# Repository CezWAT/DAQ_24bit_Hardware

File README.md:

# DAQ_24bit
Simple 4 channel 24bit USB DAQ
Uses ADS122U04 ADC and MCP2200 UART/GPIO - USB converter. No Dedicated uC.
4 Input channels with 4 ranges (+- 1V, 2V, 10V, 25V) and 2 current output channels.

Project for fun and curiosity with a purpose to make a simple yte precise USB DAQ without a dedicated controller requireig firmware. 

Forked to add an Eagle based pcb made by myself.

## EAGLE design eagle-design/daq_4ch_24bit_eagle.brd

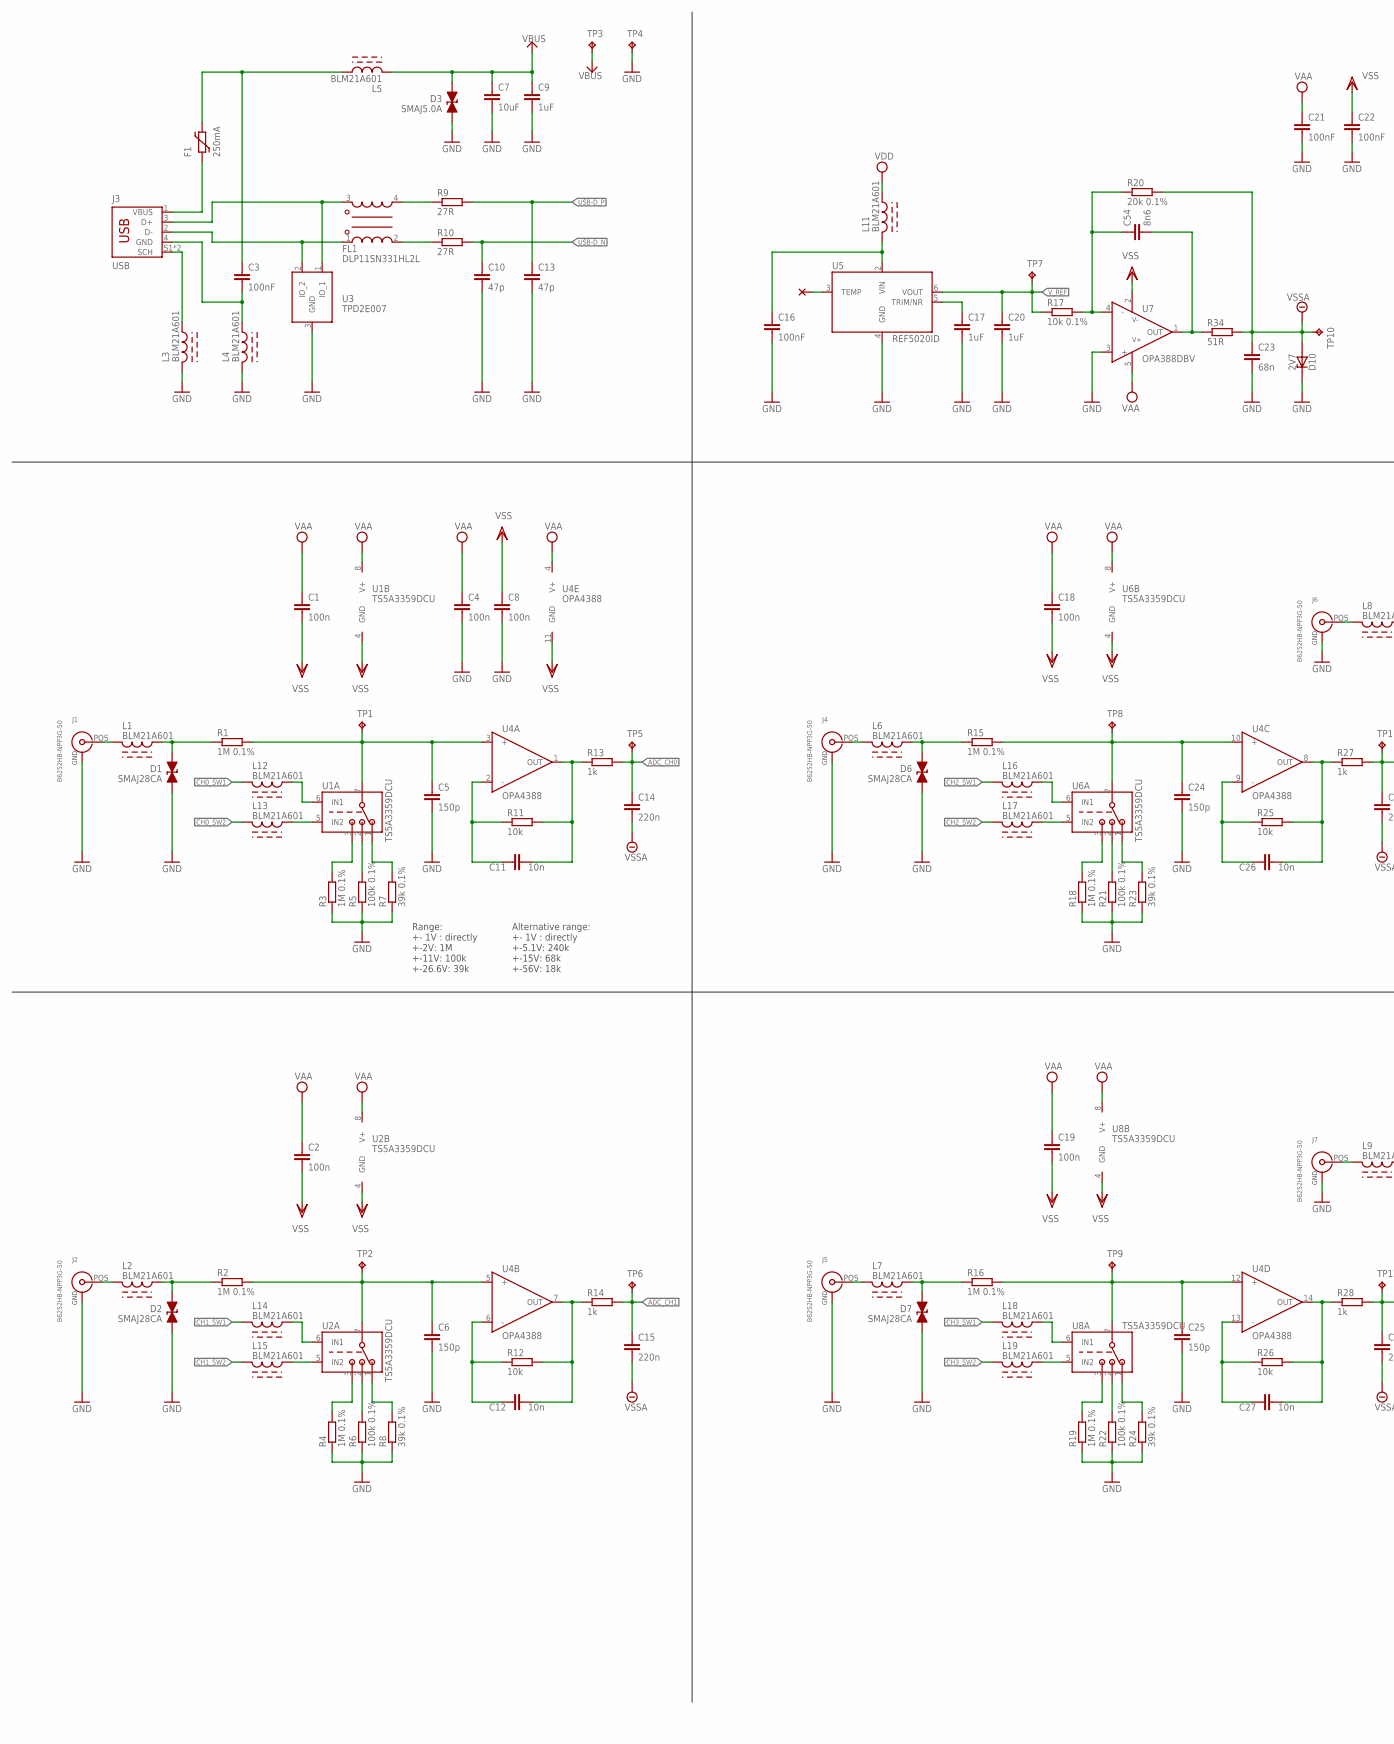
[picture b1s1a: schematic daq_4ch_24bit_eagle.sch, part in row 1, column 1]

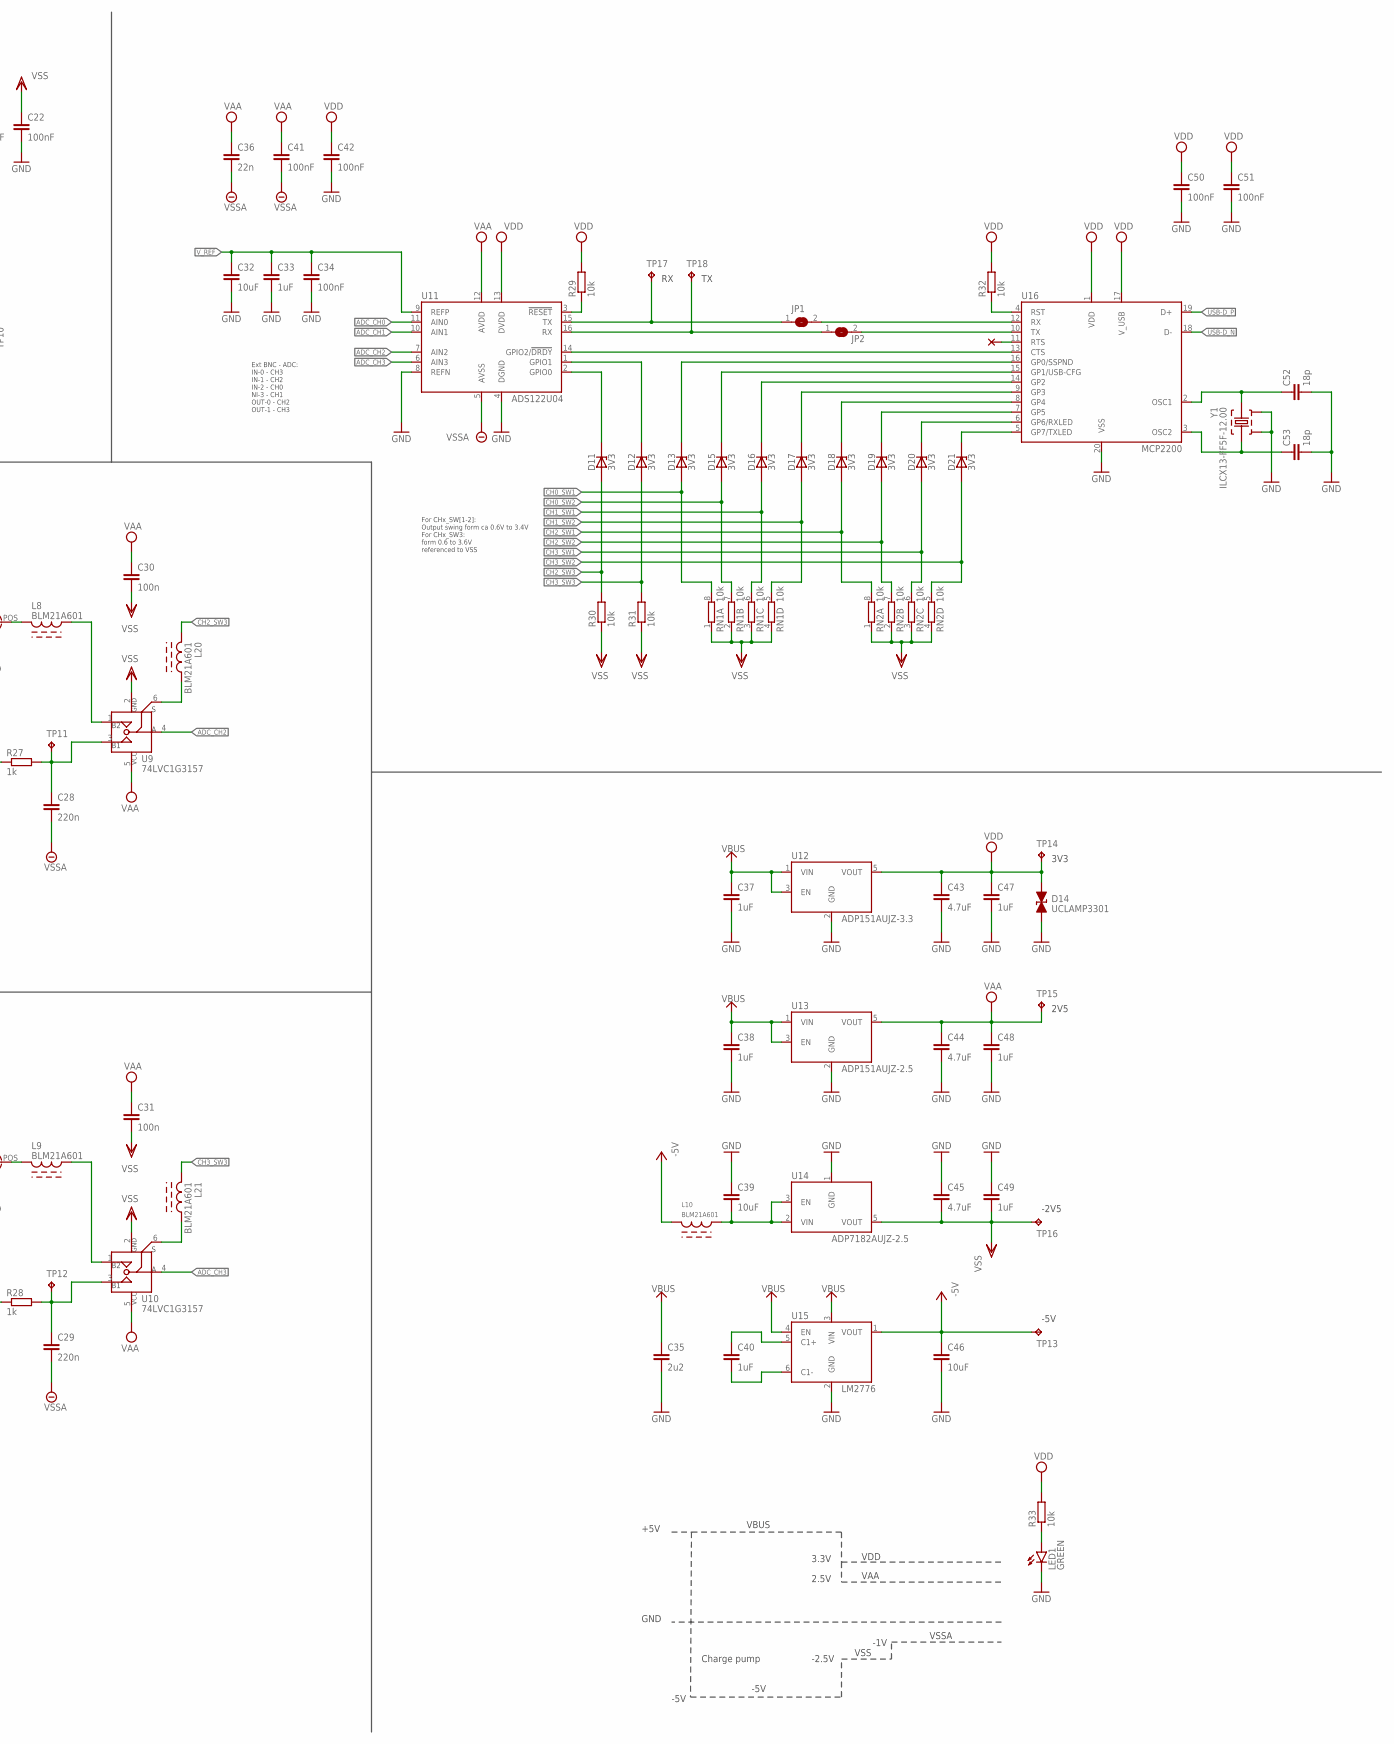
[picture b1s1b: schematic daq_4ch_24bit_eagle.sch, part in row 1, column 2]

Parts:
C1, C2, C4, C8, C18, C19, C30, C31: 100n; C0603
C3, C16, C21, C22, C34, C41, C42, C50, C51: 100nF; C0603
C5, C6, C24, C25: 150p; C0603
C7, C32, C39, C46: 10uF; C0603
C9, C17, C20, C33, C37, C38, C40, C47, C48, C49: 1uF; C0603
C10, C13: 47p; C0603
C11, C12, C26, C27: 10n; C0603
C14, C15, C28, C29: 220n; C0603
C23: 68n; C0603
C35: 2u2; C0603
C36: 22n; C0603
C43, C44, C45: 4.7uF; C0603
C52, C53: 18p; C0603
C54: 8n6; C0603
D1, D2, D6, D7: SMAJ28CA; SMA(UNI)
D3: SMAJ5.0A; SMA(UNI)
D10: 2V7; SOD323
D11, D12, D13, D15, D16, D17, D18, D19, D20, D21: 3V3; SOD323
D14: UCLAMP3301; SOD323
F1: 250mA; 1812L
FL1: DLP11SN331HL2L
J1, J2, J4, J5, J6, J7: B6252HB-NPP3G-50
J3: USB; USB_B_THT
JP1, JP2: SJ
L1, L2, L3, L4, L5, L6, L7, L8, L9, L10, L11, L12, L13, L14, L15, L16, L17, L18, L19, L20, L21: BLM21A601; L0805
LED1: GREEN; LED5MM
R1, R2, R3, R4, R15, R16, R18, R19: 1M 0.1%; R0603
R5, R6, R21, R22: 100k 0.1%; R0603
R7, R8, R23, R24: 39k 0.1%; R0603
R9, R10: 27R; R0603
R11, R12, R25, R26, R29, R30, R31, R32, R33: 10k; R0603
R13, R14, R27, R28: 1k; R0603
R17: 10k 0.1%; R0603
R20: 20k 0.1%; R0603
R34: 51R; R0603
RN1, RN2: 10k; 0603-ARV
TP1, TP2, TP3, TP4, TP5, TP6, TP7, TP8, TP9, TP10, TP11, TP12, TP14: 3V3; B1,27
TP13: -5V; B1,27
TP15: 2V5; B1,27
TP16: -2V5; B1,27
TP17: RX; B1,27
TP18: TX; B1,27
U1, U2, U6, U8: TS5A3359DCU; DCU
U3: TPD2E007; SOT323
U4: OPA4388; SOIC14
U5: REF5020ID; SOIC8
U7: OPA388DBV; SOT23-5
U9, U10: 74LVC1G3157; SOT23-6
U11: ADS122U04; SSOP16
U12: ADP151AUJZ-3.3; SOT23-5
U13: ADP151AUJZ-2.5; SOT23-5
U14: ADP7182AUJZ-2.5; SOT23-5
U15: LM2776; SOT23-6
U16: MCP2200; SSOP20
Y1: ILCX13-FF5F-12.00; ILCX13

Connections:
-5V: C46.1, L10.1, TP13.TP, U15.1 (VOUT)
ADC_CH0: C14.1, R13.2, TP5.TP, U11.11 (AIN0)
ADC_CH1: C15.1, R14.2, TP6.TP, U11.10 (AIN1)
ADC_CH2: U9.4 (A), U11.7 (AIN2)
ADC_CH3: U10.4 (A), U11.6 (AIN3)
CH0_SW1: D13.A, L12.1, RN1.8 (2)
CH0_SW2: D15.A, L13.1, RN1.7 (2)
CH1_SW1: D16.A, L14.1, RN1.6 (2)
CH1_SW2: D17.A, L15.1, RN1.5 (2)
CH2_SW1: D18.A, L16.1, RN2.8 (2)
CH2_SW2: D19.A, L17.1, RN2.7 (2)
CH2_SW3: D11.A, L20.1, R30.2
CH3_SW1: D20.A, L18.1, RN2.6 (2)
CH3_SW2: D21.A, L19.1, RN2.5 (2)
CH3_SW3: D12.A, L21.1, R31.2
GND: C4.2, C5.2, C6.2, C7.2, C8.2, C9.2, C10.2, C13.2, C16.2, C17.2, C20.2, C21.2, C22.2, C23.2, C24.2, C25.2, C32.2, C33.2, C34.2, C35.2, C37.2, C38.2, C39.1, C42.2, C43.2, C44.2, C45.1, C46.2, C47.2, C48.2, C49.1, C50.2, C51.2, C52.2, C53.2, D1.2, D2.2, D3.2, D6.2, D7.2, D10.C, D14.C (2), J1.2 (GND), J1.3 (GND), J1.4 (GND), J2.2 (GND), J2.3 (GND), J2.4 (GND), J4.2 (GND), J4.3 (GND), J4.4 (GND), J5.2 (GND), J5.3 (GND), J5.4 (GND), J6.2 (GND), J6.3 (GND), J6.4 (GND), J7.2 (GND), J7.3 (GND), J7.4 (GND), L3.1, L4.1, LED1.K (C), R3.1, R4.1, R5.1, R6.1, R7.1, R8.1, R18.1, R19.1, R21.1, R22.1, R23.1, R24.1, TP4.TP, U3.3 (GND), U5.4 (GND), U7.3 (+), U11.4 (DGND), U11.8 (REFN), U12.2 (GND), U13.2 (GND), U14.1 (GND), U15.2 (GND), U16.20 (VSS), Y1.2, Y1.4
unnamed: C40.1, U15.5 (C1+)
unnamed: C40.2, U15.6 (C1-)
unnamed: C39.2, L10.2, U14.2 (VIN), U14.3 (EN)
unnamed: D21.C, U16.5 (GP7/TXLED)
unnamed: D20.C, U16.6 (GP6/RXLED)
unnamed: D19.C, U16.7 (GP5)
unnamed: D18.C, U16.8 (GP4)
unnamed: D17.C, U16.9 (GP3)
unnamed: D16.C, U16.14 (GP2)
unnamed: D15.C, U16.15 (GP1/USB-CFG)
unnamed: D13.C, U16.16 (GP0/SSPND)
unnamed: D11.C, U11.2 (GPIO0)
unnamed: D12.C, U11.1 (GPIO1)
unnamed: JP2.1, TP18.TP, U11.16 (RX)
unnamed: JP1.1, TP17.TP, U11.15 (TX)
unnamed: R32.1, U16.4 (RST)
unnamed: JP1.2, U16.12 (RX)
unnamed: JP2.2, U16.10 (TX)
unnamed: U11.14 (GPIO2/!DRDY), U16.13 (CTS)
unnamed: R29.1, U11.3 (!RESET)
unnamed: LED1.A, R33.1
unnamed: C3.1, F1.2, L5.2
unnamed: J3.S1 (SCH), J3.S2 (SCH), L3.2
unnamed: FL1.2, R10.1
unnamed: FL1.4, R9.1
unnamed: C16.1, L11.1, U5.2 (VIN)
unnamed: C17.1, U5.5 (TRIM/NR)
unnamed: C54.2, R34.1, U7.1 (OUT)
unnamed: C54.1, R17.2, R20.1, U7.4 (-)
unnamed: C52.1, U16.2 (OSC1), Y1.1
unnamed: C53.1, U16.3 (OSC2), Y1.3
unnamed: J1.POS, L1.1
unnamed: D1.1, L1.2, R1.1
unnamed: C11.2, R11.2, R13.1, U4.1 (OUT)
unnamed: R5.2, U1.2 (NO1)
unnamed: L13.2, U1.5 (IN2)
unnamed: L12.2, U1.6 (IN1)
unnamed: C5.1, R1.2, TP1.TP, U1.7 (COM), U4.3 (+)
unnamed: R7.2, U1.1 (NO0)
unnamed: R3.2, U1.3 (NO2)
unnamed: C11.1, R11.1, U4.2 (-)
unnamed: J4.POS, L6.1
unnamed: D6.1, L6.2, R15.1
unnamed: L17.2, U6.5 (IN2)
unnamed: L16.2, U6.6 (IN1)
unnamed: C24.1, R15.2, TP8.TP, U4.10 (+), U6.7 (COM)
unnamed: R21.2, U6.2 (NO1)
unnamed: R23.2, U6.1 (NO0)
unnamed: R18.2, U6.3 (NO2)
unnamed: C26.2, R25.2, R27.1, U4.8 (OUT)
unnamed: C26.1, R25.1, U4.9 (-)
unnamed: C28.1, R27.2, TP11.TP, U9.3 (B1)
unnamed: J6.POS, L8.1
unnamed: L8.2, U9.1 (B2)
unnamed: L20.2, U9.6 (S)
unnamed: J2.POS, L2.1
unnamed: D2.1, L2.2, R2.1
unnamed: L15.2, U2.5 (IN2)
unnamed: L14.2, U2.6 (IN1)
unnamed: C6.1, R2.2, TP2.TP, U2.7 (COM), U4.5 (+)
unnamed: R6.2, U2.2 (NO1)
unnamed: R8.2, U2.1 (NO0)
unnamed: R4.2, U2.3 (NO2)
unnamed: C12.2, R12.2, R14.1, U4.7 (OUT)
unnamed: C12.1, R12.1, U4.6 (-)
unnamed: J5.POS, L7.1
unnamed: D7.1, L7.2, R16.1
unnamed: L19.2, U8.5 (IN2)
unnamed: L18.2, U8.6 (IN1)
unnamed: C25.1, R16.2, TP9.TP, U4.12 (+), U8.7 (COM)
unnamed: R22.2, U8.2 (NO1)
unnamed: R24.2, U8.1 (NO0)
unnamed: R19.2, U8.3 (NO2)
unnamed: C27.2, R26.2, R28.1, U4.14 (OUT)
unnamed: C27.1, R26.1, U4.13 (-)
unnamed: C29.1, R28.2, TP12.TP, U10.3 (B1)
unnamed: J7.POS, L9.1
unnamed: L9.2, U10.1 (B2)
unnamed: L21.2, U10.6 (S)
USB-D_N: C10.1, R10.2, U16.18 (D-)
USB-D_P: C13.1, R9.2, U16.19 (D+)
USBD_N: FL1.1, J3.2 (D-), U3.2 (IO_2)
USBD_P: FL1.3, J3.3 (D+), U3.1 (IO_1)
USBGND: C3.2, J3.4 (GND), L4.2
VAA: C1.1, C2.1, C4.1, C18.1, C19.1, C21.1, C30.1, C31.1, C36.1, C41.1, C44.1, C48.1, TP15.TP, U1.8 (V+), U2.8 (V+), U4.4 (V+), U6.8 (V+), U7.5 (V+), U8.8 (V+), U9.5 (VCC), U10.5 (VCC), U11.12 (AVDD), U13.5 (VOUT)
VBUS: C7.1, C9.1, C35.1, C37.1, C38.1, D3.1, L5.1, TP3.TP, U12.1 (VIN), U12.3 (EN), U13.1 (VIN), U13.3 (EN), U15.3 (VIN), U15.4 (EN)
VDD: C42.1, C43.1, C47.1, C50.1, C51.1, D14.A (1), L11.2, R29.2, R32.2, R33.2, TP14.TP, U11.13 (DVDD), U12.5 (VOUT), U16.1 (VDD), U16.17 (V_USB)
VSS: C1.2, C2.2, C8.1, C18.2, C19.2, C22.1, C30.2, C31.2, C45.2, C49.2, R30.1, R31.1, RN1.1, RN1.2 (1), RN1.3 (1), RN1.4 (1), RN2.1, RN2.2 (1), RN2.3 (1), RN2.4 (1), TP16.TP, U1.4 (GND), U2.4 (GND), U4.11 (GND), U6.4 (GND), U7.2 (GND), U8.4 (GND), U9.2 (GND), U10.2 (GND), U14.5 (VOUT)
VSSA: C14.2, C15.2, C23.1, C28.2, C29.2, C36.2, C41.2, D10.A, R20.2, R34.2, TP10.TP, U11.5 (AVSS)
VUSB: F1.1, J3.1 (VBUS)
V_REF: C20.1, C32.1, C33.1, C34.1, R17.1, TP7.TP, U5.6 (VOUT), U11.9 (REFP)

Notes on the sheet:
For CHx_SW[1-2]: Output swing form ca 0.6V to 3.4V For CHx_SW3: form 0.6 to 3.6V referenced to VSS
Ext BNC - ADC: IN-0 - CH3 IN-1 - CH2 IN-2 - CH0 NI-3 - CH1 OUT-0 - CH2 OUT-1 - CH3
3V3
2V5
-2V5
-5V
GND
+5V
VBUS
3.3V
2.5V
VDD
VAA
Charge pump
-2.5V
VSS
-1V
VSSA
Alternative range: +- 1V : directly +-5.1V: 240k +-15V: 68k +-56V: 18k
Range: +- 1V : directly +-2V: 1M +-11V: 100k +-26.6V: 39k

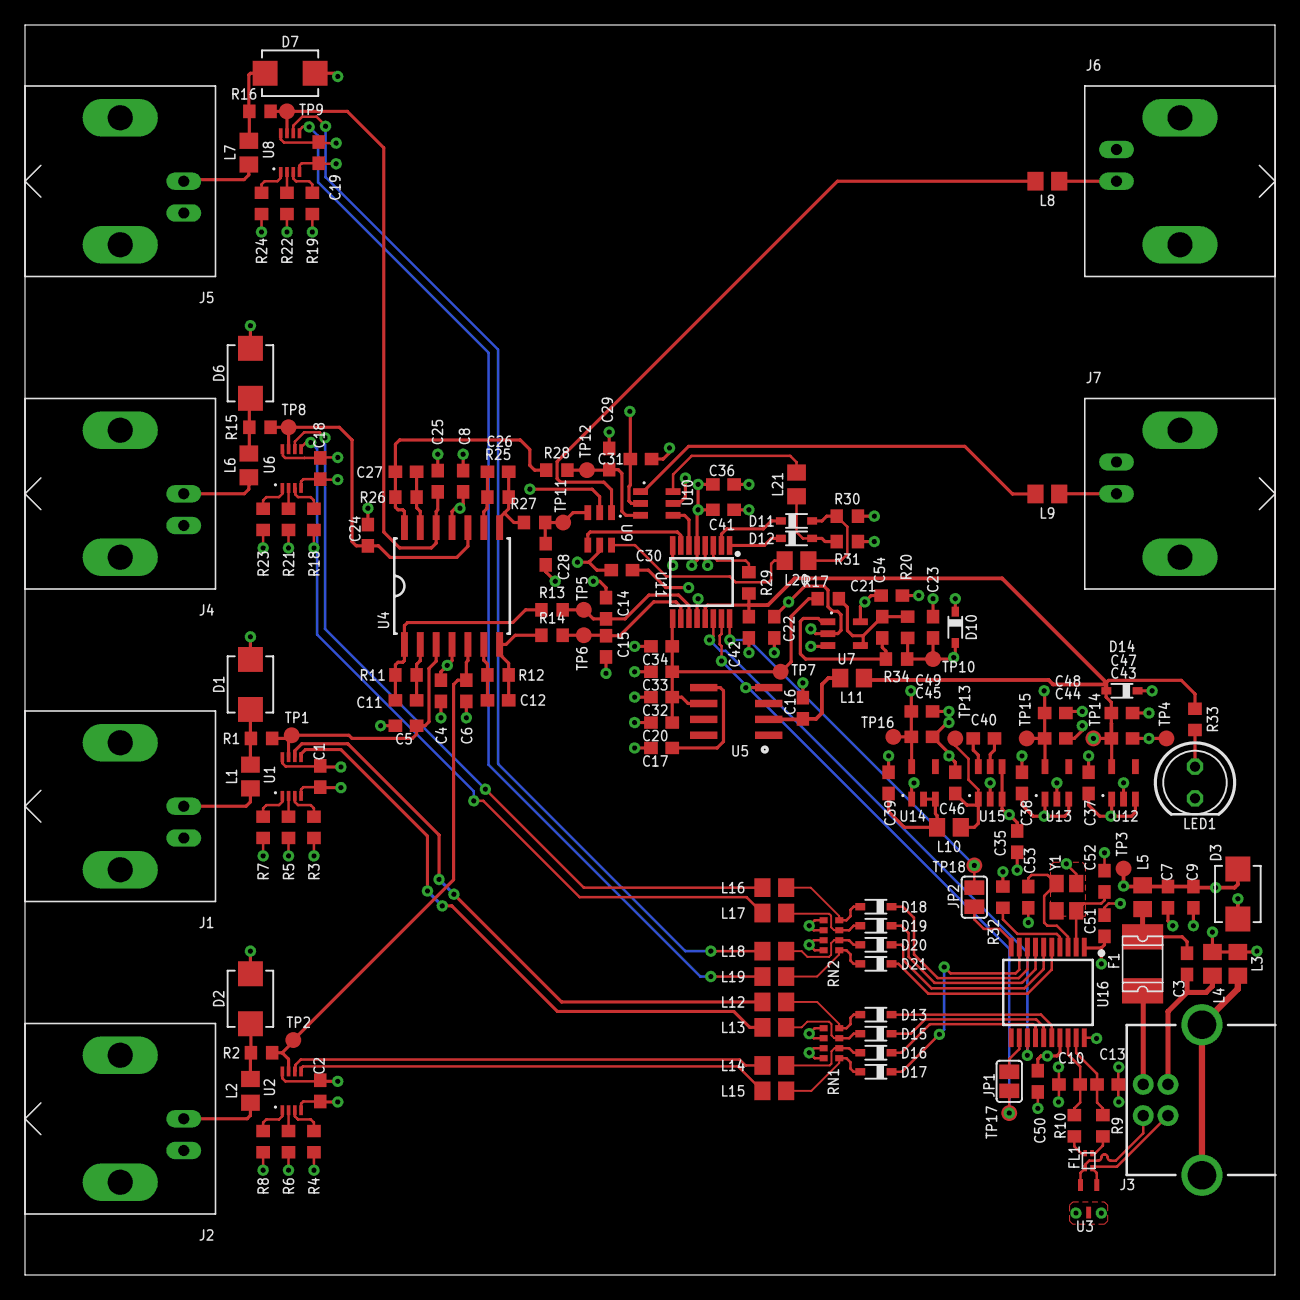
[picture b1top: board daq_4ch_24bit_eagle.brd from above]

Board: 4 copper layers, 100.0 x 100.0 mm, 175 parts (0 on the bottom side), 107 nets.

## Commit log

2020-11-27 Add schematic & library in eagle, generated pcb from sch
2020-12-12 Fixes to schematic and library, begin placement and routing
2020-12-16 Fix on schematic, placement and routing done, needs impendance calculation, first iteration - could be improved
